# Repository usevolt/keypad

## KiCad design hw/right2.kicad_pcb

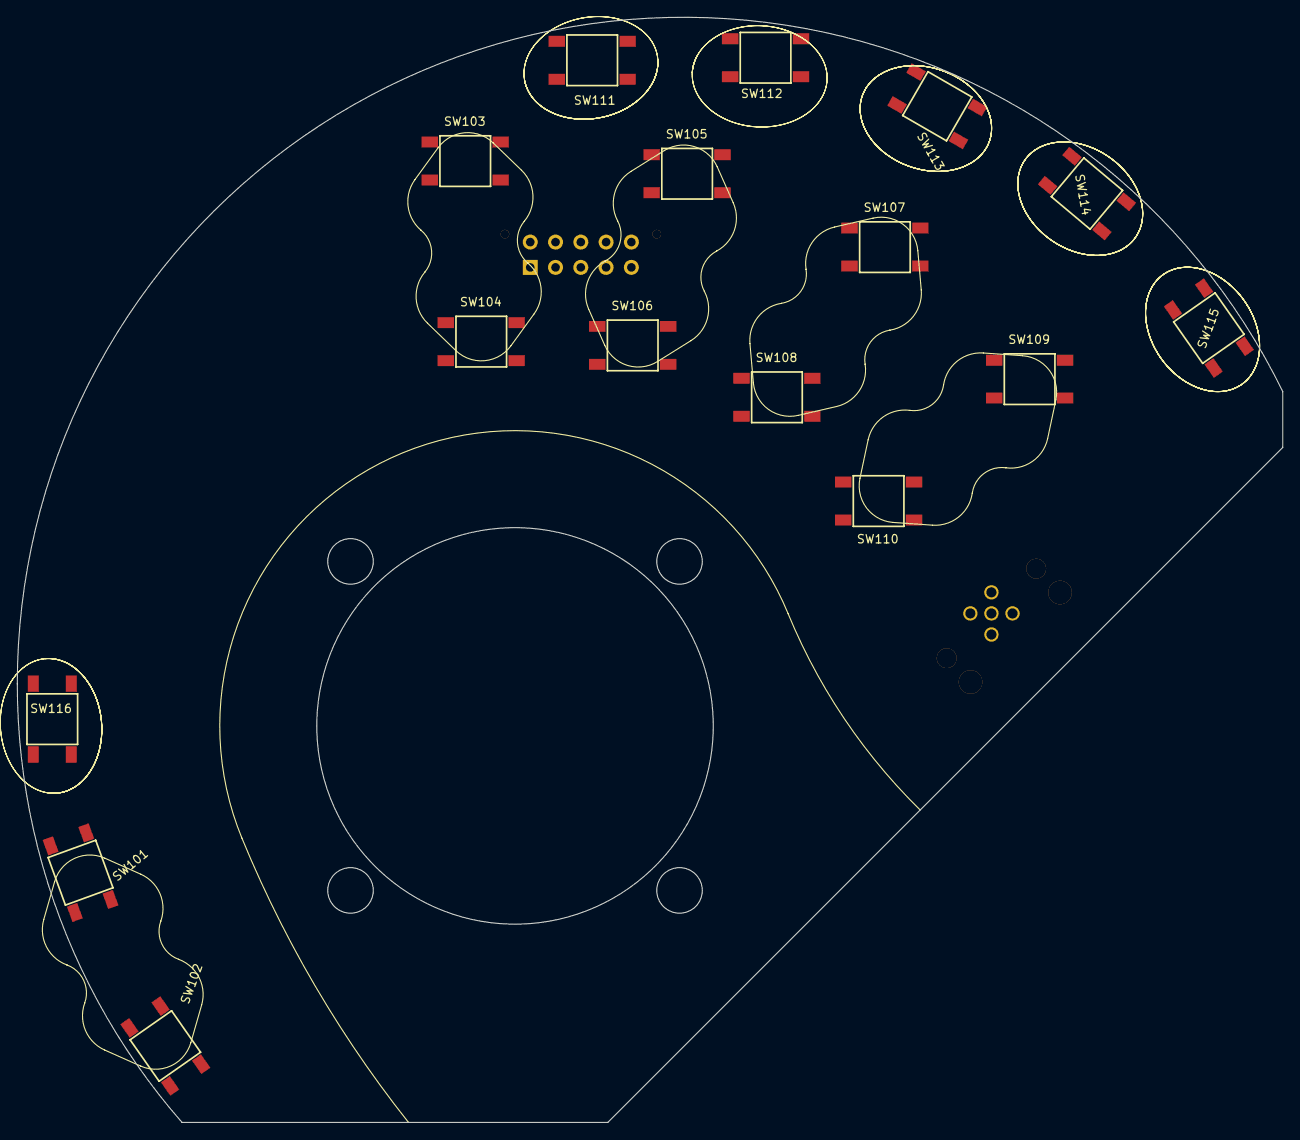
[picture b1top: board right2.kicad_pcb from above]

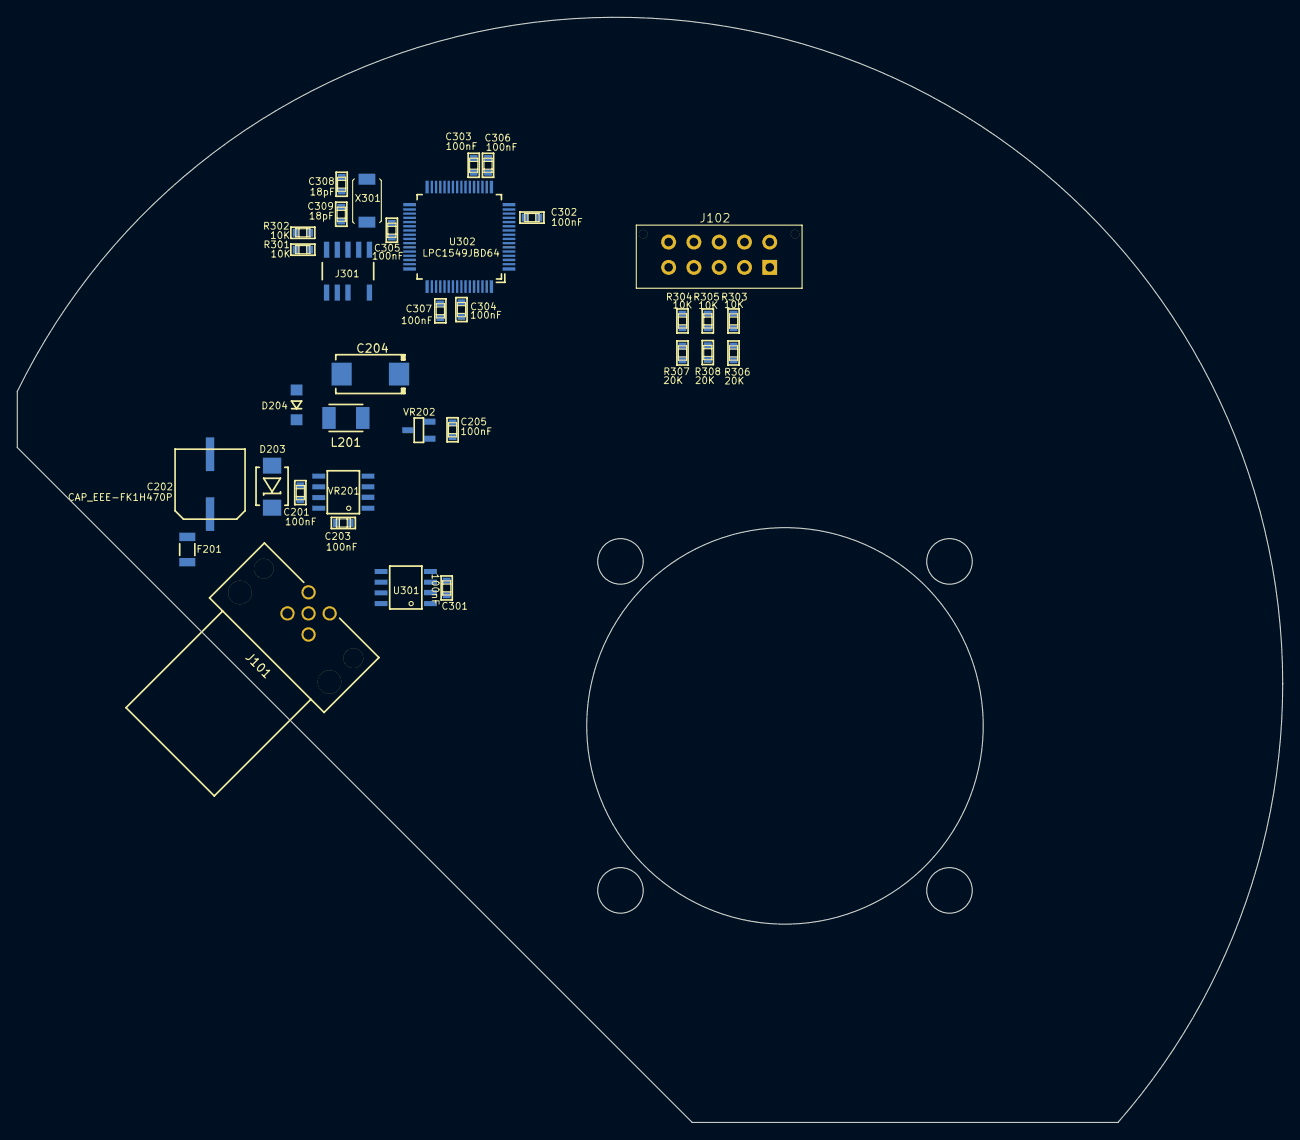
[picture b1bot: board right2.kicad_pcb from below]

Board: 2 copper layers, 150.0 x 131.0 mm, 50 parts (34 on the bottom side), 38 nets, no tracks yet.

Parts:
C201, C203, C205, C301, C302, C303, C304, C305, C306, C307: 100nF; 0603
C202: CAP_EEE-FK1H470P
C204: T491D226K035AT; 7343
C308, C309: 18pF; 0603
D203: DIODE_TVS_SMBJ33A-TRDO-214AA; DO-214AA
D204: DIODE_RS07J-GS18; DO219AB
F201: FUSE_MC36211_350MA; FUSE_MC36211
J101: M12_5P_MALE_ANG_43-01205
J102: MOLEX_MICRO-FIT_10WAY_V
J301: ARM_JTAG_SWD_HEADER_10_PINSMD; ARM_10_PIN_JTAG_SWD_CONNECTOR
L201: IND_744045210
R301, R302, R303, R304, R305: 10K; 0603
R306, R307, R308: 20K; 0603
SW101, SW102, SW103, SW104, SW105, SW106, SW107, SW108, SW109, SW110, SW111, SW112, SW113, SW114, SW115, SW116: SWITCH_PTS645SM43SMTR92
U301: MCP2551_SOIC8; SOIC8
U302: LPC1549JBD64; QFP64
VR201: LM2671SOIC8; SOIC8
VR202: REG_MCP1700; SOT-23_3-PIN
X301: XTAL_7A-12.000MAAJ-T; XTAL_7A-20.000MAJ

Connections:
+3V3: C205.1, C302.1, C303.1, C304.1, C305.1, C306.1, C307.1, J301.P$1, R301.2, R302.2, U302.P$13, U302.P$18, U302.P$20, U302.P$22, U302.P$37, U302.P$52, U302.P$57, VR202.P$2
+5V: C204.+, C301.1, J102.P$1, J102.P$4, J102.P$7, L201.2, U301.3, VR201.4, VR202.P$3
/CANH: J101.4, U301.7
/CANL: J101.5, U301.6
/Sheet5A1EB8D2/VIN: F201.P$1, J101.2
/Sheet5A1EB78A/B1: SW101.1, SW101.2, U302.P$7
/Sheet5A1EB78A/B2: SW109.1, SW109.2, U302.P$62
/Sheet5A1EB78A/B3: SW102.1, SW102.2, U302.P$8
/Sheet5A1EB78A/B4: SW110.1, SW110.2, U302.P$61
/Sheet5A1EB78A/B5: SW103.1, SW103.2, U302.P$9
/Sheet5A1EB78A/B6: SW111.1, SW111.2, U302.P$5
/Sheet5A1EB78A/B7: SW104.1, SW104.2, U302.P$10
/Sheet5A1EB78A/B8: SW112.1, SW112.2, U302.P$4
/Sheet5A1EB78A/B9: SW105.1, SW105.2, U302.P$11
/Sheet5A1EB78A/B10: SW113.1, SW113.2, U302.P$3
/Sheet5A1EB78A/B11: SW106.1, SW106.2, U302.P$12
/Sheet5A1EB78A/B12: SW114.1, SW114.2, U302.P$2
/Sheet5A1EB78A/B13: SW107.1, SW107.2, U302.P$28
/Sheet5A1EB78A/B14: SW115.1, SW115.2, U302.P$1
/Sheet5A1EB78A/B15: SW108.1, SW108.2, U302.P$46
/Sheet5A1EB78A/B16: SW116.1, SW116.2, U302.P$6
/Sheet5A1EB78A/CAN_RX: U301.4, U302.P$59
/Sheet5A1EB78A/CAN_TX: U301.1, U302.P$60
/Sheet5A1EB78A/RESET: J301.P$9, U302.P$45
/Sheet5A1EB78A/X: J102.P$2, R303.1
/Sheet5A1EB78A/Y: J102.P$5, R304.1
/Sheet5A1EB78A/Z: J102.P$8, R305.1
GND: C201.2, C202.-, C204.-, C205.2, C301.2, C302.2, C303.2, C304.2, C305.2, C306.2, C307.2, C308.2, C309.2, D203.P$1, D204.P$1, J101.3, J102.P$3, J102.P$6, J102.P$9, J301.P$3, J301.P$5, R306.1, R307.1, R308.1, SW101.3, SW101.4, SW102.3, SW102.4, SW103.3, SW103.4, SW104.3, SW104.4, SW105.3, SW105.4, SW106.3, SW106.4, SW107.3, SW107.4, SW108.3, SW108.4, SW109.3, SW109.4, SW110.3, SW110.4, SW111.3, SW111.4, SW112.3, SW112.4, SW113.3, SW113.4, SW114.3, SW114.4, SW115.3, SW115.4, SW116.3, SW116.4, U301.2, U301.8, U302.P$14, U302.P$21, U302.P$26, U302.P$27, U302.P$41, U302.P$55, U302.P$56, VR201.6, VR202.P$1
unnamed: C201.1, C202.+, D203.P$2, F201.P$2, VR201.7
unnamed: C203.1, VR201.1
unnamed: C203.2, D204.P$2, L201.1, VR201.8
unnamed: C308.1, U302.P$35, X301.P$1
unnamed: C309.1, U302.P$36, X301.P$2
unnamed: J301.P$2, R301.1, U302.P$44
unnamed: J301.P$4, R302.1, U302.P$40
unnamed: R303.2, R306.2, U302.P$31
unnamed: R304.2, R307.2, U302.P$33
unnamed: R305.2, R308.2, U302.P$32

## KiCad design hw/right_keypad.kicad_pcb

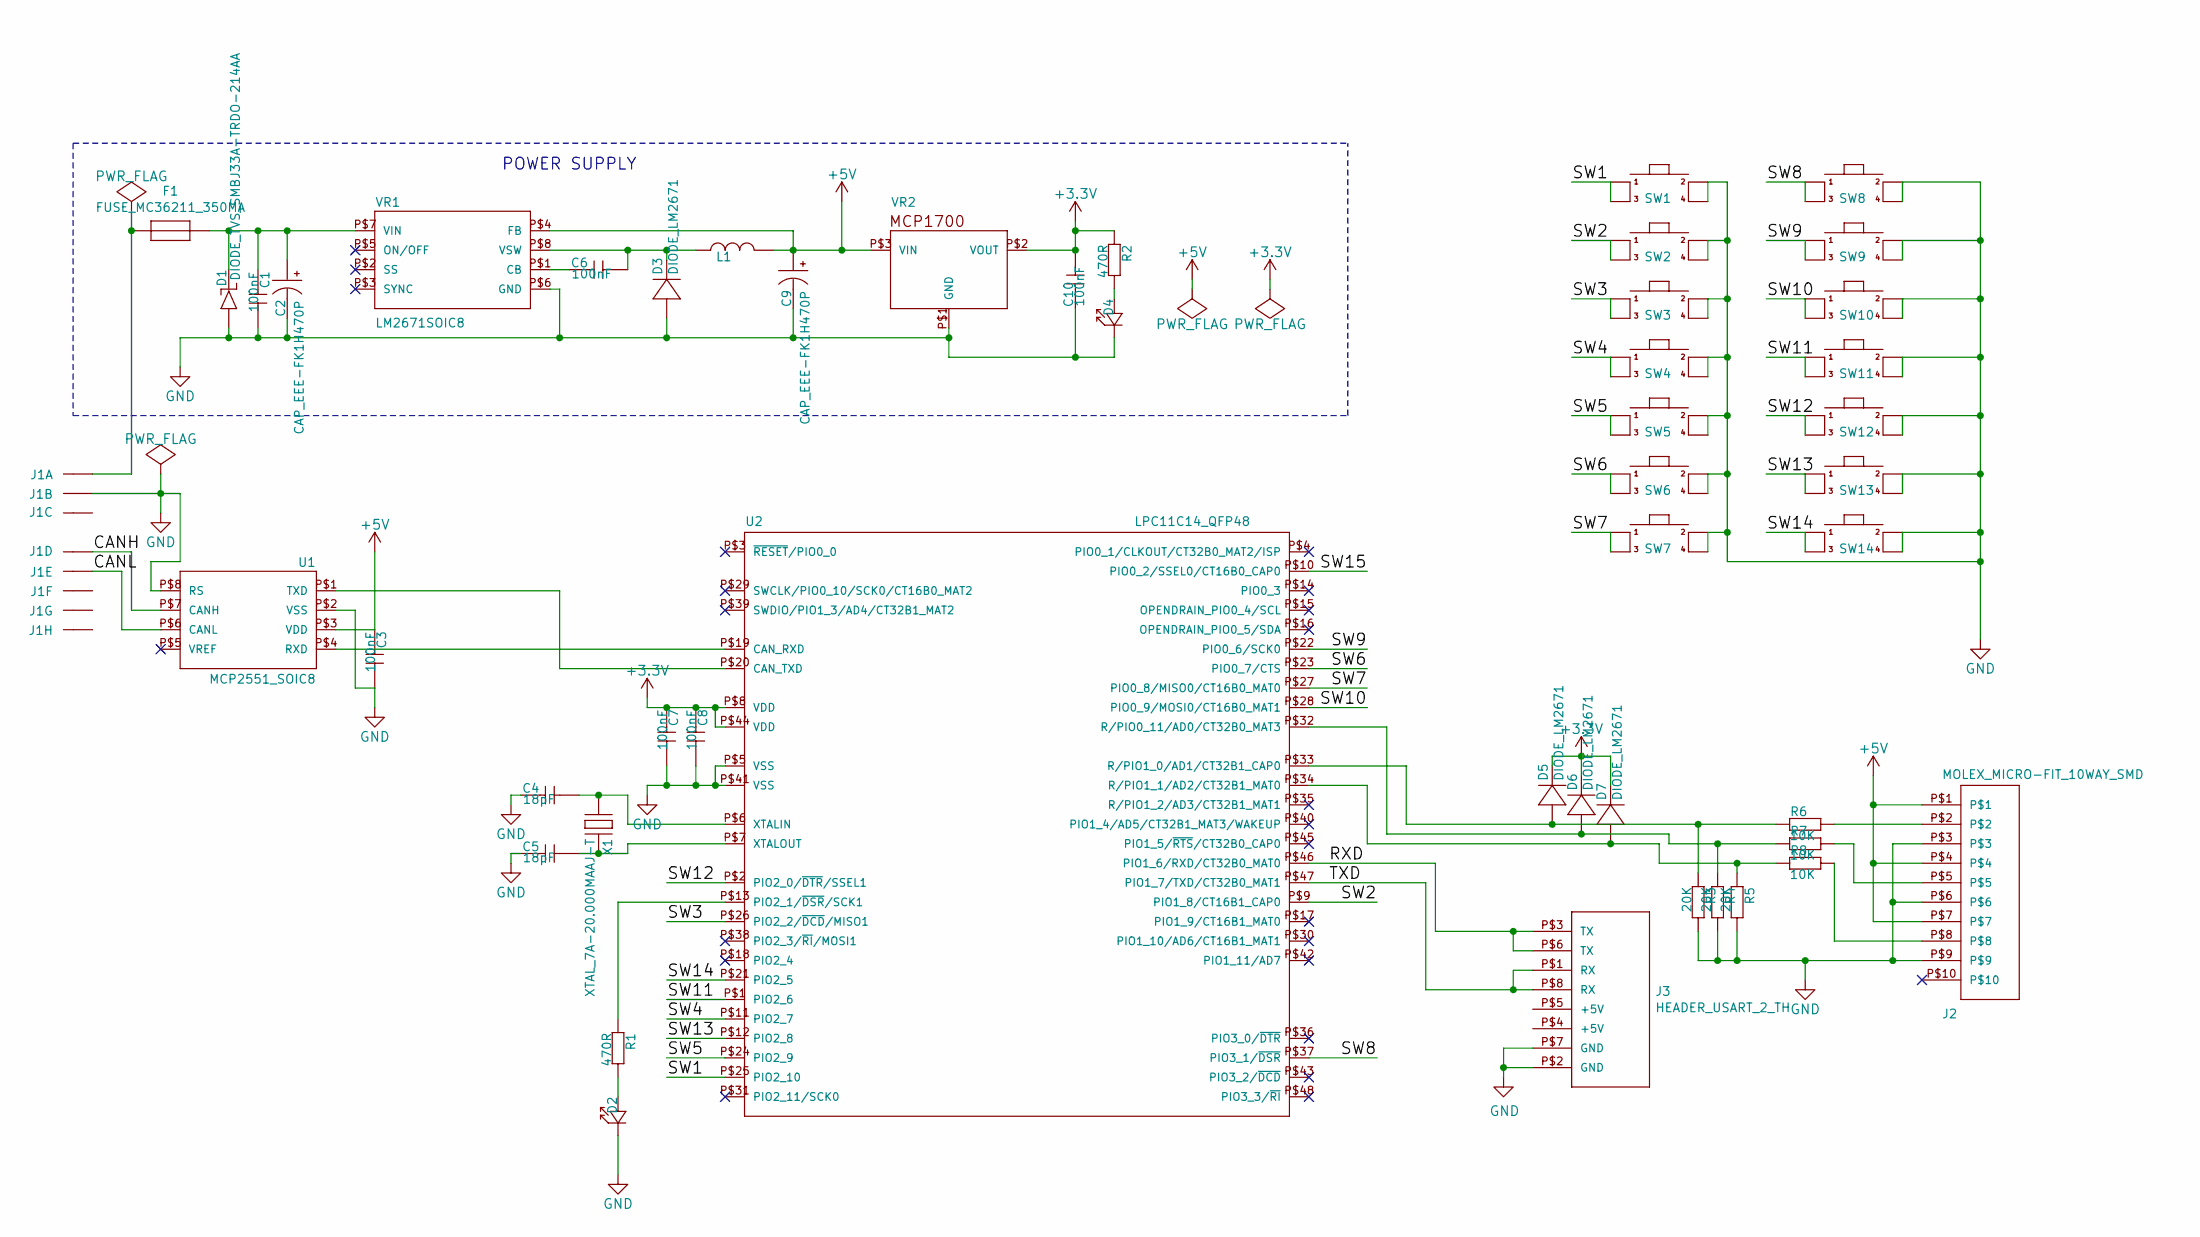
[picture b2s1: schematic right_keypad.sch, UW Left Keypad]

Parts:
C1, C3, C6, C7, C8, C10: 100nF; 0603; Manufacturer Part Number C0603C104K5RACTU
C2, C9: CAP_EEE-FK1H470P; Manufacturer Part Number EEE-FK1H470P
C4, C5: 18pF; 0603; Manufacturer Part Number C0603C180J2GACTU
D1: DIODE_TVS_SMBJ33A-TRDO-214AA; DO-214AA; Manufacturer Part Number SMBJ33A
D2, D4: WL-SMCW-150060BS75000-B; 0603; Manufacturer Part Number 150060BS75000
D3, D5, D6, D7: DIODE_LM2671; DO219AB; Manufacturer Part Number RS07J-GS18
F1: FUSE_MC36211_350MA; FUSE_MC36211; Manufacturer Part Number MC36211
J1: AMPSEAL_8_POS_776275-1; Manufacturer Part Number 776275-1
J2: MOLEX_MICRO-FIT_10WAY_SMD; MOLEX_MICRO-FIT_10WAY_V; Manufacturer Part Number 43045-1027
J3: HEADER_USART_2_TH
L1: INDUCTOR_SDR1005-101KL; INDUCTOR_BOURNS_10X13X5MM; Manufacturer Part Number SDR1005-101KL
R1, R2: 470R; 0603; Manufacturer Part Number MC0063W06031470R
R3, R4, R5: 20K; 0603; Manufacturer Part Number MC0063W0603120K
R6, R7, R8: 10K; 0603; Manufacturer Part Number MC0063W0603110K
SW1, SW2, SW3, SW4, SW5, SW6, SW7, SW8, SW9, SW10, SW11, SW12, SW13, SW14: SWITCH_B3W-4050; Manufacturer Part Number B3W-4050
U1: MCP2551_SOIC8; SOIC8; Manufacturer Part Number MCP2551-I/SN
U2: LPC11C14_QFP48; QFP48; Manufacturer Part Number LPC11C14FBD48/301
VR1: LM2671SOIC8; SOIC8; Manufacturer Part Number LM2671M-5.0/NOPB
VR2: REG_MCP1700; SOT-23_3-PIN; Manufacturer Part Number MCP1700T-3302E/TT
X1: XTAL_7A-20.000MAAJ-T; XTAL_7A-20.000MAJ; Manufacturer Part Number 7A-20.000MAAJ-T

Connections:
+3V3: C7.1 (C1), C8.1 (C1), C10.2 (C2), D5.P$2 (N), D6.P$2 (N), D7.P$2 (N), R2.2 (R2), U2.P$8 (VDD), U2.P$44 (VDD), VR2.P$2 (VOUT)
+5V: C3.1 (C1), C9.+, J2.P$1, J2.P$4, J2.P$7, L1.P$2, U1.P$3 (VDD), VR1.P$4 (FB), VR2.P$3 (VIN)
/CANH: J1.P$4, U1.P$7 (CANH)
/CANL: J1.P$5, U1.P$6 (CANL)
/RXD: J3.P$3 (TX), J3.P$6 (TX), U2.P$46 (PIO1_6/RXD/CT32B0_MAT0)
/SW1: SW1.P$1, SW1.P$2, U2.P$25 (PIO2_10)
/SW2: SW2.P$1, SW2.P$2, U2.P$9 (PIO1_8/CT16B1_CAP0)
/SW3: SW3.P$1, SW3.P$2, U2.P$26 (PIO2_2/~DCD~/MISO1)
/SW4: SW4.P$1, SW4.P$2, U2.P$11 (PIO2_7)
/SW5: SW5.P$1, SW5.P$2, U2.P$24 (PIO2_9)
/SW6: SW6.P$1, SW6.P$2, U2.P$23 (PIO0_7/CTS)
/SW7: SW7.P$1, SW7.P$2, U2.P$27 (PIO0_8/MISO0/CT16B0_MAT0)
/SW8: SW8.P$1, SW8.P$2, U2.P$37 (PIO3_1/~DSR)
/SW9: SW9.P$1, SW9.P$2, U2.P$22 (PIO0_6/SCK0)
/SW10: SW10.P$1, SW10.P$2, U2.P$28 (PIO0_9/MOSI0/CT16B0_MAT1)
/SW11: SW11.P$1, SW11.P$2, U2.P$1 (PIO2_6)
/SW12: SW12.P$1, SW12.P$2, U2.P$2 (PIO2_0/~DTR~/SSEL1)
/SW13: SW13.P$1, SW13.P$2, U2.P$12 (PIO2_8)
/SW14: SW14.P$1, SW14.P$2, U2.P$21 (PIO2_5)
/TXD: J3.P$1 (RX), J3.P$8 (RX), U2.P$47 (PIO1_7/TXD/CT32B0_MAT1)
GND: C1.2 (C2), C2.-, C3.2 (C2), C4.1 (C1), C5.1 (C1), C7.2 (C2), C8.2 (C2), C9.-, C10.1 (C1), D1.P$1, D2.1 (K), D3.P$1, D4.1 (K), J1.P$2, J2.P$3, J2.P$6, J2.P$9, J3.P$2 (GND), J3.P$7 (GND), R3.1 (R1), R4.1 (R1), R5.1 (R1), SW1.P$3, SW1.P$4, SW2.P$3, SW2.P$4, SW3.P$3, SW3.P$4, SW4.P$3, SW4.P$4, SW5.P$3, SW5.P$4, SW6.P$3, SW6.P$4, SW7.P$3, SW7.P$4, SW8.P$3, SW8.P$4, SW9.P$3, SW9.P$4, SW10.P$3, SW10.P$4, SW11.P$3, SW11.P$4, SW12.P$3, SW12.P$4, SW13.P$3, SW13.P$4, SW14.P$3, SW14.P$4, U1.P$2 (VSS), U1.P$8 (RS), U2.P$5 (VSS), U2.P$41 (VSS), VR1.P$6 (GND), VR2.P$1 (GND)
unnamed: C1.1 (C1), C2.+, D1.P$2 (N), F1.P$2, VR1.P$7 (VIN)
unnamed: C4.2 (C2), U2.P$6 (XTALIN), X1.P$1
unnamed: C5.2 (C2), U2.P$7 (XTALOUT), X1.P$2
unnamed: C6.1 (C1), VR1.P$1 (CB)
unnamed: C6.2 (C2), D3.P$2 (N), L1.P$1, VR1.P$8 (VSW)
unnamed: D2.2 (A), R1.1 (R1)
unnamed: D4.2 (A), R2.1 (R1)
unnamed: D5.P$1, R3.2 (R2), R6.2 (R2), U2.P$33 (R/PIO1_0/AD1/CT32B1_CAP0)
unnamed: D6.P$1, R4.2 (R2), R7.2 (R2), U2.P$32 (R/PIO0_11/AD0/CT32B0_MAT3)
unnamed: D7.P$1, R5.2 (R2), R8.2 (R2), U2.P$34 (R/PIO1_1/AD2/CT32B1_MAT0)
unnamed: F1.P$1, J1.P$1
unnamed: J2.P$2, R6.1 (R1)
unnamed: J2.P$5, R7.1 (R1)
unnamed: J2.P$8, R8.1 (R1)
unnamed: R1.2 (R2), U2.P$13 (PIO2_1/~DSR~/SCK1)
unnamed: U1.P$1 (TXD), U2.P$20 (CAN_TXD)
unnamed: U1.P$4 (RXD), U2.P$19 (CAN_RXD)

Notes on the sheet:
POWER SUPPLY

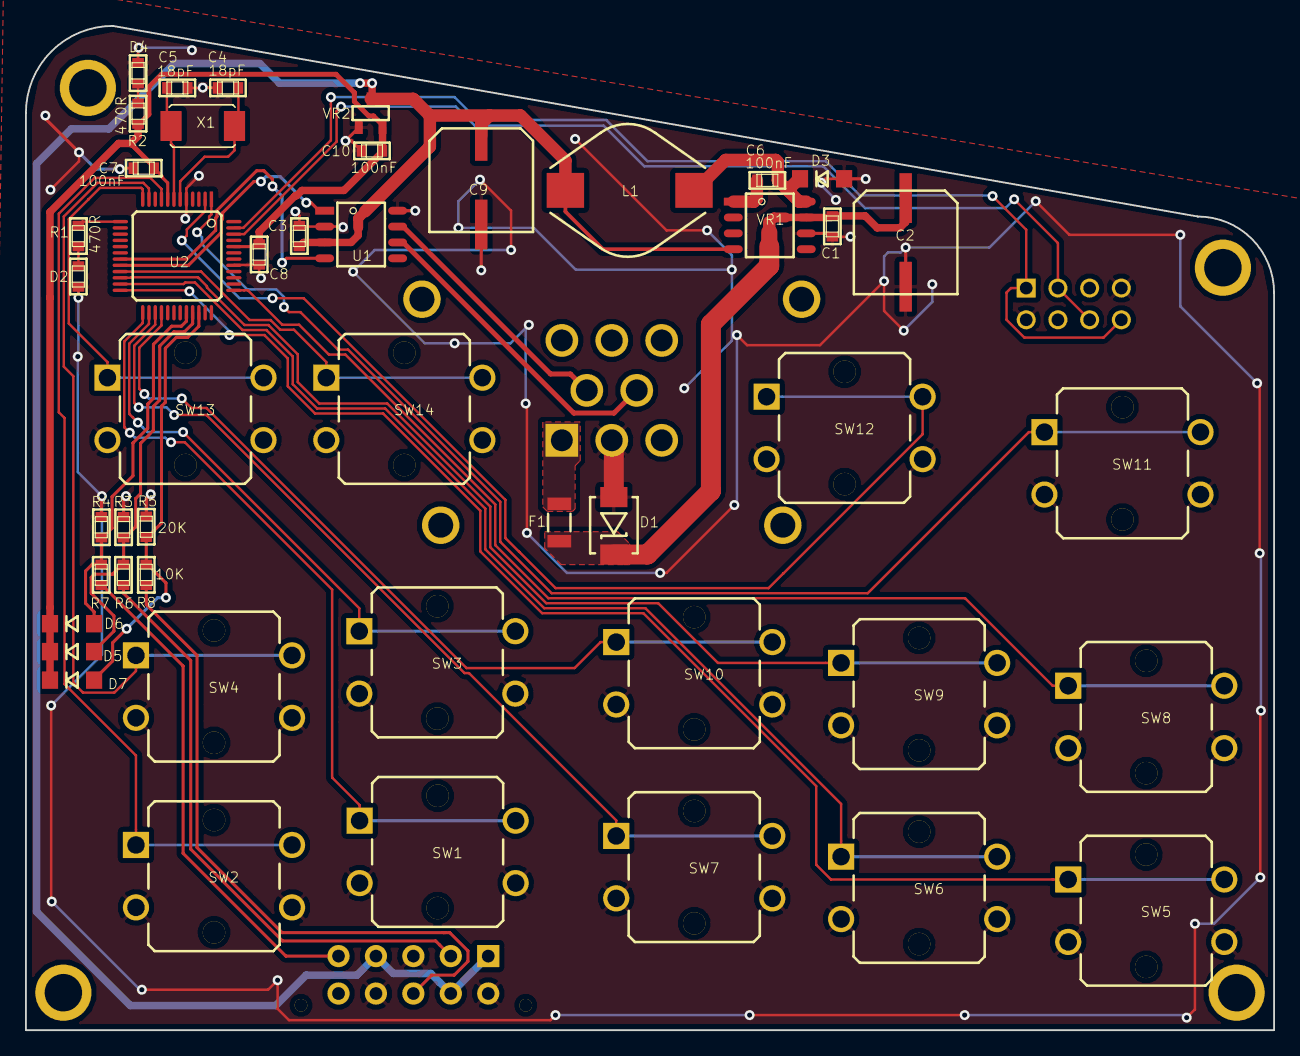
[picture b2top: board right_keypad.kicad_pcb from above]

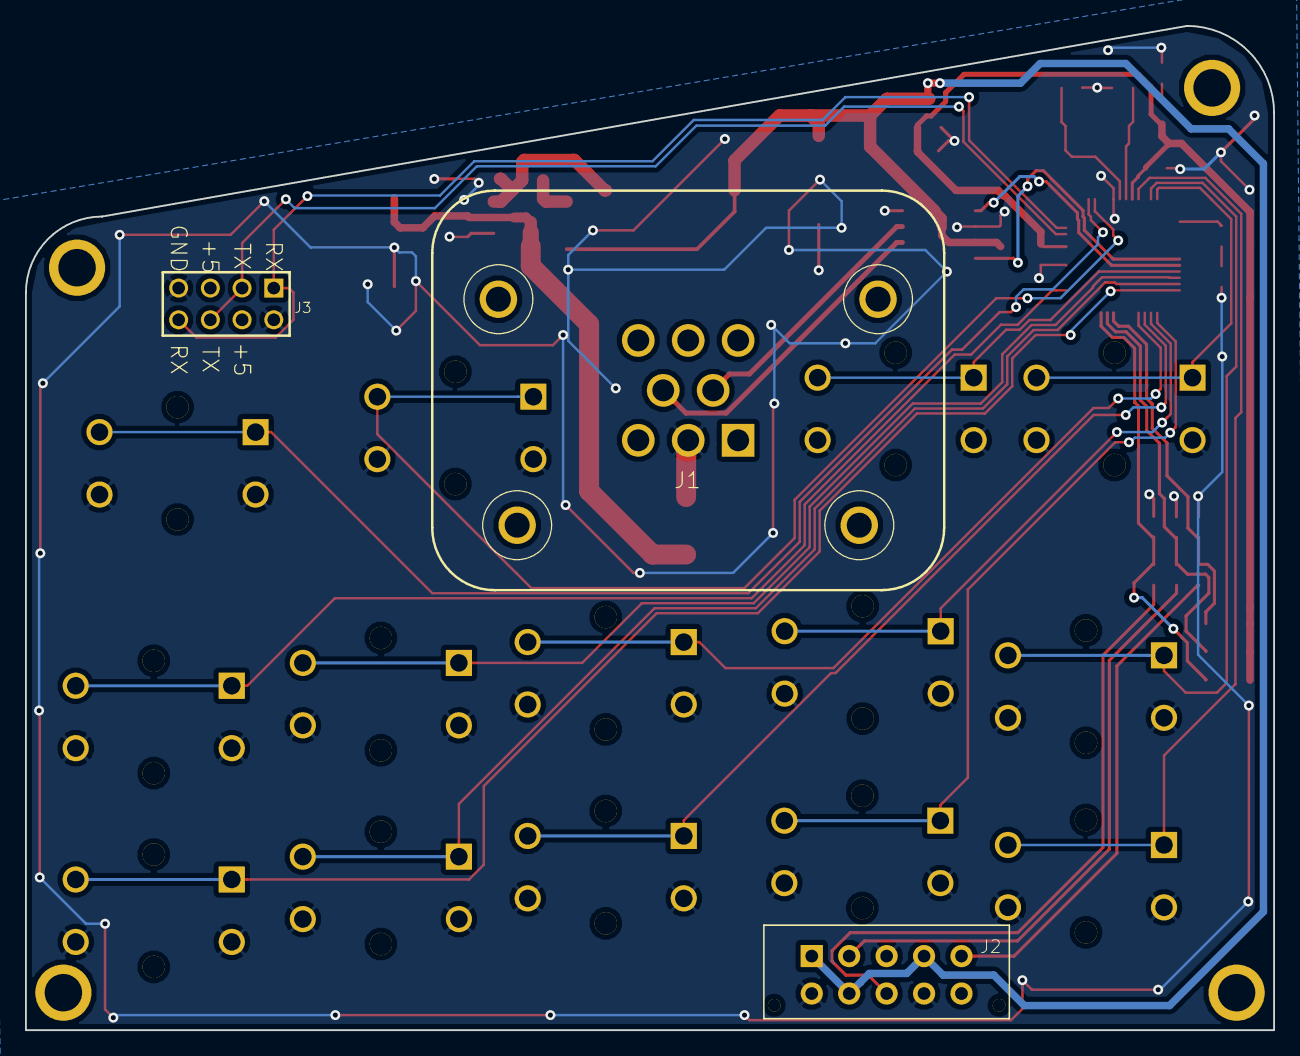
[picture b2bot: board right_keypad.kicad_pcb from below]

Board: 2 copper layers, 99.9 x 80.4 mm, 49 parts (3 on the bottom side), 38 nets.

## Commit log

2016-02-23 Add initial SW and HW files
    - copy sw & hw versions 0.5, 1.0 & 1.1 from svn version control
    - change hal library paths to point into LPC11C14 in version_control/hal
2016-03-03 Add 1.0, 1.1 & 1.2 HW versions to version control
    - They were missing from last commit
2016-03-28 Add 2.0 and 3.0 HW versions
2016-04-30 version 3.0 hardware drawn
2016-05-18 Keypad files modified to use build-time configurable uw_hal library
2016-05-18 Deleted old HW revision files
2016-06-16 HW revision 3.0
2016-06-19 developing HW version 4.0
2016-07-04 implementing the next version of HW
2016-07-04 hal library changed from uw to uv
2016-09-08 Designing the kicad version of hw
2016-10-24 revision 5 ordered from itead
2016-12-22 implementing firmware for 5.0 hw
2017-01-04 Added .gitmodules for hal submodule
2017-01-04 binary files removed from repo
2017-01-04 gitmodules removed
2017-01-04 HAL submodule included in the version control
2017-01-04 tx buffer updated to CAN hal
2017-01-04 deleted object files
2017-01-04 makefile .map moved to object directory
2017-01-25 Created covers and ordered them from shapeways
2017-02-08 ordupdated enclosures to have 4 round buttons instead of 2 switches
2017-03-10 not working version with renewed object dictionary interface
2017-03-11 pcb hw revision 5 software with new obj dict interface
2017-03-28 hw but 5 & 6 rotated 20 degrees to fit their places
2017-03-31 axis calibration available only if axis has no active error
2017-04-01 screw hole pocket radius increased
2017-04-04 axis calibration min & max value added threshold
    Hopefully reduced hazards, since min cannot be greater or equal to middle value, same for max.
2017-04-11 bug fix: Axis calib msb obj's array length corrected
2017-05-18 enclosure bug fixes:
    2 outermost button's rotation corrected
    cover's border thickness increased for good 3d print manufacturing
2017-06-27 enclosure plane thickness is now constant 1.0 mm
2017-07-10 added OTTO JHM model and created assembly file
2017-07-12 version 3 top collar ordered from shapeways
2017-12-17 drawing right2 pcb
2018-08-27 sw compiles without dependencies to lpcxpresso
2018-08-27 button count reduced, b5, 6, 7 grouped together
2019-01-26 stencil gerbers created from old keypads
2019-06-02 button plastics updated to imaterialise ordering
2019-06-02 keypads can revive from bus off
2019-10-09 submodule urls set to https github
2021-10-26 covers without buttons step and stl created
